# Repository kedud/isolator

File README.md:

# Isolator

This module acts as a kind of crossover filter. The 3 potentiometers allow to attenuate or amplify any of the desired frequencies ranges.

The BoM for this schematics can be found [here](https://octopart.com/bom-tool/y1pE2aPx)

A Mouser cart is also available [here](https://www.mouser.com/ProjectManager/ProjectDetail.aspx?AccessID=a37104b332)

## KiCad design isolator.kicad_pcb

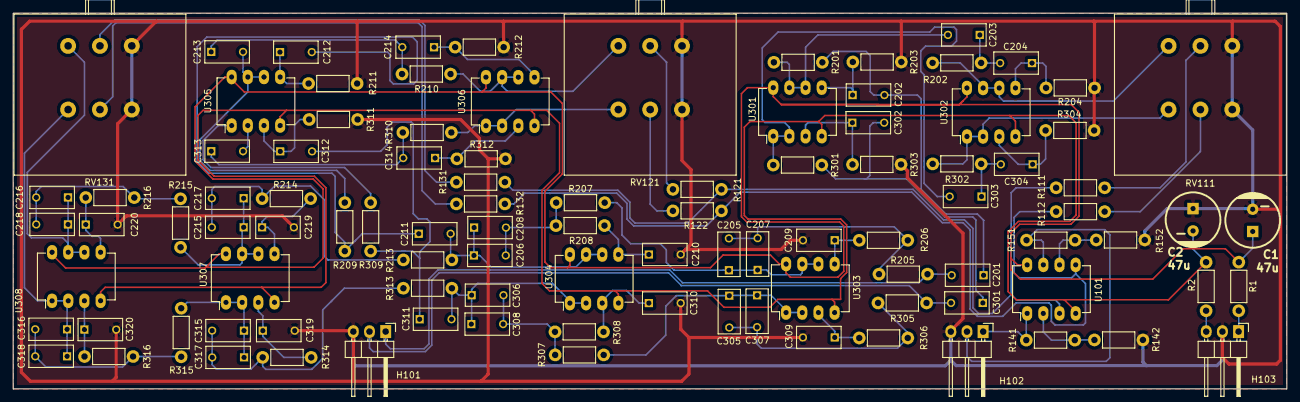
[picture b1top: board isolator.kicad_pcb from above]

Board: 2 copper layers, 200.0 x 59.0 mm, 101 parts (0 on the bottom side), 67 nets.

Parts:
C1, C2: 47u; CP_8x11.5mm
C201, C202, C203, C204, C205, C206, C207, C208, C209, C210, C301, C302, C303, C304, C305, C306, C307, C308, C309, C310: 3n3; C_Rect_L7_W3.5_P5
C211, C212, C213, C214, C215, C216, C217, C218, C219, C220, C311, C312, C313, C314, C315, C316, C317, C318, C319, C320: 33n; C_Rect_L7_W3.5_P5
H101, H102, H103: Header_01x03; Pin_Header_Angled_1x03
R1, R2: 100; Resistor_Horizontal_RM7mm
R111, R112, R121, R122, R131, R132: 100K; Resistor_Horizontal_RM7mm
R141, R151: 470K; Resistor_Horizontal_RM7mm
R142, R152: 47K; Resistor_Horizontal_RM7mm
R201, R202, R205, R206, R207, R208, R209, R210, R213, R214, R215, R216, R301, R302, R305, R306, R307, R308, R309, R310, R313, R314, R315, R316: 11K; Resistor_Horizontal_RM7mm
R203, R204, R211, R212, R303, R304, R311, R312: 22K; Resistor_Horizontal_RM7mm
RV111, RV121, RV131: 100K; Potentiometer_ALPS_RK27112A0A16
U101, U301, U302, U303, U304, U305, U306, U307, U308: NE5532; DIP-8_W7.62mm_LongPads

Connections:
/Left_channel/OUT_HIGH: R302.1, RV111.4, U302.1, U302.2
/Left_channel/OUT_LOW: C316.1, C318.1, RV131.4, U308.1, U308.2
/Left_channel/OUT_MID: R310.1, RV121.4, U306.1, U306.2
/Left_in: C201.2, H101.1, R205.2
/Left_output: H102.2, R151.1, U101.7
/Right_channel/OUT_HIGH: R202.1, RV111.1, U302.6, U302.7
/Right_channel/OUT_LOW: C216.1, C218.1, RV131.1, U308.6, U308.7
/Right_channel/OUT_MID: R210.1, RV121.1, U306.6, U306.7
/Right_in: C301.2, H101.2, R305.2
/Right_output: H102.1, R141.1, U101.1
GND: C1.2, C2.1, C209.2, C210.2, C219.2, C220.2, C309.2, C310.2, C319.2, C320.2, H101.3, H102.3, H103.2, R142.2, R152.2, R203.2, R204.2, R211.2, R212.2, R303.2, R304.2, R311.2, R312.2, RV111.3, RV111.6, RV121.3, RV121.6, RV131.3, RV131.6
unnamed: C201.1, C202.2, R201.2
unnamed: C202.1, R203.1, U301.5
unnamed: C203.1, C204.2, R202.2
unnamed: C203.2, R201.1, U301.6, U301.7
unnamed: C204.1, R204.1, U302.5
unnamed: C205.1, C207.1, R207.2, U303.6, U303.7
unnamed: C205.2, C207.2, R205.1, R206.2
unnamed: C206.1, C208.1, C211.2, R213.2, U304.6, U304.7
unnamed: C206.2, C208.2, R207.1, R208.2
unnamed: C209.1, R206.1, U303.5
unnamed: C210.1, R208.1, U304.5
unnamed: C211.1, C212.2, R209.2
unnamed: C212.1, R211.1, U305.5
unnamed: C213.1, C214.2, R210.2
unnamed: C213.2, R209.1, U305.6, U305.7
unnamed: C214.1, R212.1, U306.5
unnamed: C215.1, C217.1, R215.2, U307.6, U307.7
unnamed: C215.2, C217.2, R213.1, R214.2
unnamed: C216.2, C218.2, R215.1, R216.2
unnamed: C219.1, R214.1, U307.5
unnamed: C220.1, R216.1, U308.5
unnamed: C301.1, C302.2, R301.2
unnamed: C302.1, R303.1, U301.3
unnamed: C303.1, C304.2, R302.2
unnamed: C303.2, R301.1, U301.1, U301.2
unnamed: C304.1, R304.1, U302.3
unnamed: C305.1, C307.1, R307.2, U303.1, U303.2
unnamed: C305.2, C307.2, R305.1, R306.2
unnamed: C306.1, C308.1, C311.2, R313.2, U304.1, U304.2
unnamed: C306.2, C308.2, R307.1, R308.2
unnamed: C309.1, R306.1, U303.3
unnamed: C310.1, R308.1, U304.3
unnamed: C311.1, C312.2, R309.2
unnamed: C312.1, R311.1, U305.3
unnamed: C313.1, C314.2, R310.2
unnamed: C313.2, R309.1, U305.1, U305.2
unnamed: C314.1, R312.1, U306.3
unnamed: C315.1, C317.1, R315.2, U307.1, U307.2
unnamed: C315.2, C317.2, R313.1, R314.2
unnamed: C316.2, C318.2, R315.1, R316.2
unnamed: C319.1, R314.1, U307.3
unnamed: C320.1, R316.1, U308.3
unnamed: H103.1, R1.2
unnamed: H103.3, R2.1
unnamed: R111.1, R121.1, R131.1, U101.3
unnamed: R111.2, RV111.2
unnamed: R112.1, R122.1, R132.1, U101.5
unnamed: R112.2, RV111.5
unnamed: R121.2, RV121.2
unnamed: R122.2, RV121.5
unnamed: R131.2, RV131.2
unnamed: R132.2, RV131.5
unnamed: R141.2, R142.1, U101.2
unnamed: R151.2, R152.1, U101.6
V+: C1.1, R1.1, U101.8, U301.8, U302.8, U303.8, U304.8, U305.8, U306.8, U307.8, U308.8
V-: C2.2, R2.2, U101.4, U301.4, U302.4, U303.4, U304.4, U305.4, U306.4, U307.4, U308.4

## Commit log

2017-11-16 Adding active components references
2017-11-16 Updating components footprints
2017-11-16 Adding rm4-librairies to project
2017-11-16 Updating components references and properties
2017-11-16 Adding rm4-libraries as local project library
2017-11-16 Update rm4-librairies
2017-11-17 Remove unused libraries
2017-11-17 Updated components references and properties
2017-11-17 Updated components
2017-11-17 Add README.md
2017-11-17 minor components edits
